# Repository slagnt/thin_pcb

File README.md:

# thin_pcb
5x5 pcb atmega32u4 smd

<a href="https://github.com/slagnt/thin_pcb/raw/master/pdf/thin_pcb.pdf">Eeschema PDF</a>

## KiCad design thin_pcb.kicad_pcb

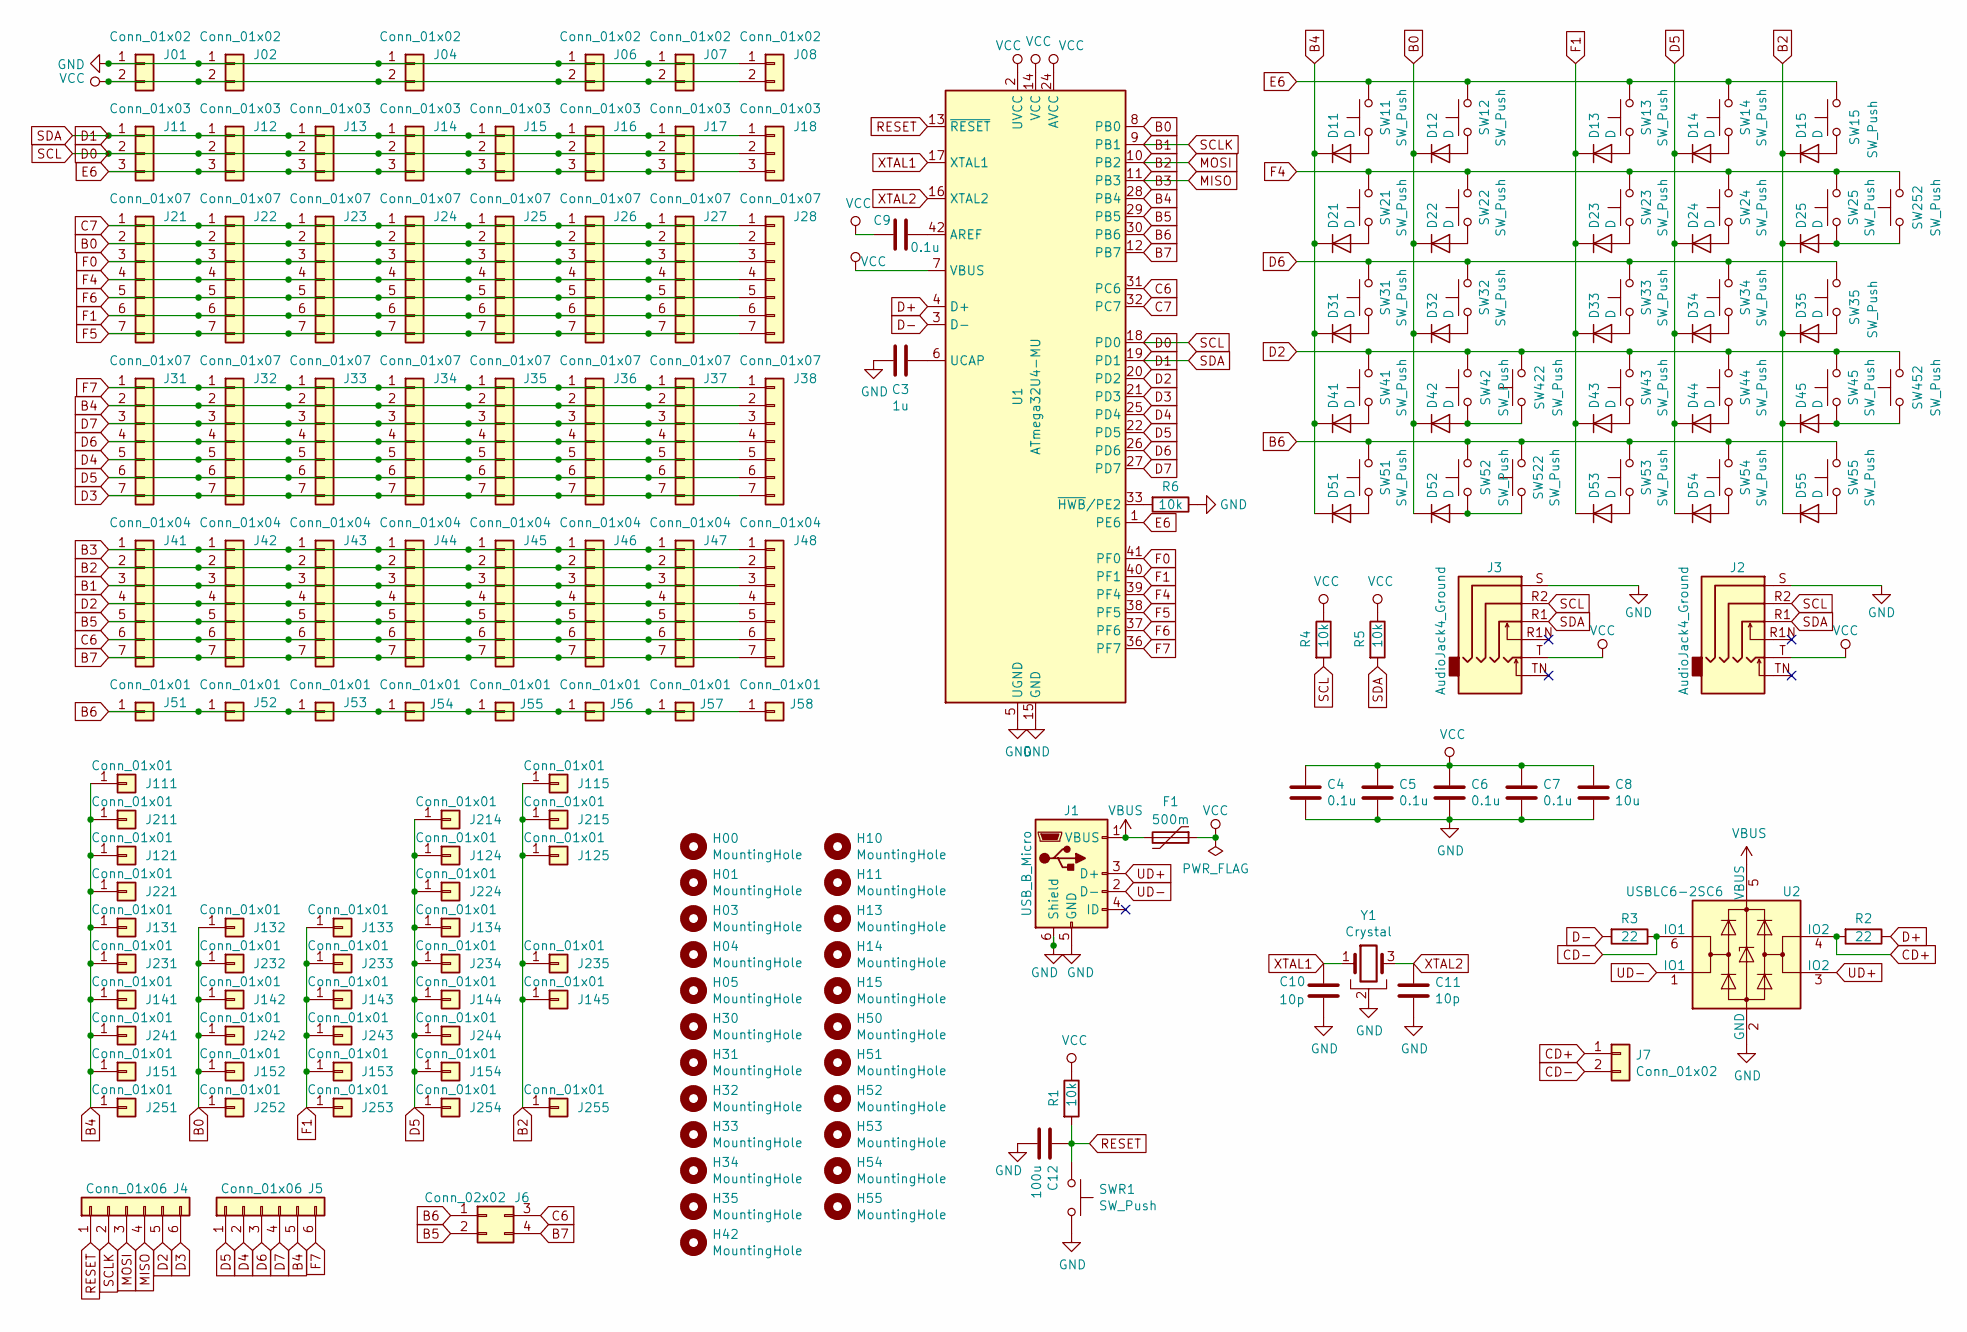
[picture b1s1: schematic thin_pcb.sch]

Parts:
C3: 1u; C_0402_1005Metric
C4, C5, C6, C7, C9: 0.1u; C_0402_1005Metric
C8: 10u; C_0402_1005Metric
C10, C11: 10p; C_0402_1005Metric
C12: 100u; C_0402_1005Metric
D11, D12, D13, D14, D15, D21, D22, D23, D24, D25, D31, D32, D33, D34, D35, D41, D42, D43, D44, D45, D51, D52, D53, D54, D55: D; D_MiniMELF
F1: 500m; Fuse_0603_1608Metric
H00, H01, H03, H04, H05, H10, H11, H13, H14, H15, H30, H31, H32, H33, H34, H35, H42, H50, H51, H52, H53, H54, H55: MountingHole; MountingHole_4mm
J1: USB_B_Micro; USB_Micro-B_Amphenol_10103594-0001LF_Horizontal
J01, J02, J04, J06, J7, J07, J08: Conn_01x02; PinSocket_1x02_P2.54mm_Vertical
J2, J3: AudioJack4_Ground; Jack_2.5mm_PJ242
J4, J5: Conn_01x06; PinSocket_1x06_P2.54mm_Vertical
J6: Conn_02x02; PinSocket_2x02_P2.54mm_Vertical
J11, J12, J13, J14, J15, J16, J17, J18: Conn_01x03; PinSocket_1x03_P2.54mm_Vertical
J21, J22, J23, J24, J25, J26, J27, J28, J31, J32, J33, J34, J35, J36, J37, J38: Conn_01x07; PinSocket_1x07_P2.54mm_Vertical
J41, J42, J43, J44, J45, J46, J47, J48: Conn_01x04; PinSocket_1x07_P2.54mm_Vertical
J51, J52, J53, J54, J55, J56, J57, J58, J111, J115, J121, J124, J125, J131, J132, J133, J134, J141, J142, J143, J144, J145, J151, J152, J153, J154, J211, J214, J215, J221, J224, J231, J232, J233, J234, J235, J241, J242, J243, J244, J251, J252, J253, J254, J255: Conn_01x01; PinSocket_1x01_P2.54mm_Vertical
R1, R4, R5, R6: 10k; R_0402_1005Metric
R2, R3: 22; R_0402_1005Metric
SW11, SW12, SW13, SW14, SW15, SW21, SW22, SW23, SW24, SW25, SW31, SW32, SW33, SW34, SW35, SW41, SW42, SW43, SW44, SW45, SW51, SW52, SW53, SW54, SW55, SW252, SW452: SW_Push; MX-Alps-Choc-1U-Mine
SW422, SW522: SW_Push; MX-Alps-Choc-1U-Mine-Flip
SWR1: SW_Push; SW_Reset
U1: ATmega32U4-MU; QFN-44-1EP_7x7mm_P0.5mm_EP5.2x5.2mm
U2: USBLC6-2SC6; SOT-23-6
Y1: Crystal; Resonator_SMD_muRata_CSTxExxV-3Pin_3.0x1.1mm

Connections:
B0: D12.1 (K), D22.1 (K), D32.1 (K), D42.1 (K), D52.1 (K), J21.2, J22.2, J23.2, J24.2, J25.2, J26.2, J27.2, J28.2, J132.1, J142.1, J152.1, J232.1, J242.1, J252.1, U1.8 (PB0)
B1: J4.2, J41.3, J42.3, J43.3, J44.3, J45.3, J46.3, J47.3, J48.3, U1.9 (PB1)
B2: D15.1 (K), D25.1 (K), D35.1 (K), D45.1 (K), D55.1 (K), J4.3, J41.2, J42.2, J43.2, J44.2, J45.2, J46.2, J47.2, J48.2, J115.1, J125.1, J145.1, J215.1, J235.1, J255.1, U1.10 (PB2)
B3: J4.4, J41.1, J42.1, J43.1, J44.1, J45.1, J46.1, J47.1, J48.1, U1.11 (PB3)
B4: D11.1 (K), D21.1 (K), D31.1 (K), D41.1 (K), D51.1 (K), J5.5, J31.2, J32.2, J33.2, J34.2, J35.2, J36.2, J37.2, J38.2, J111.1, J121.1, J131.1, J141.1, J151.1, J211.1, J221.1, J231.1, J241.1, J251.1, U1.28 (PB4)
B5: J6.2, J41.5, J42.5, J43.5, J44.5, J45.5, J46.5, J47.5, J48.5, U1.29 (PB5)
B6: J6.1, J51.1, J52.1, J53.1, J54.1, J55.1, J56.1, J57.1, J58.1, SW51.2, SW52.2, SW53.2, SW54.2, SW55.2, SW522.2, U1.30 (PB6)
B7: J6.4, J41.7, J42.7, J43.7, J44.7, J45.7, J46.7, J47.7, J48.7, U1.12 (PB7)
C6: J6.3, J41.6, J42.6, J43.6, J44.6, J45.6, J46.6, J47.6, J48.6, U1.31 (PC6)
C7: J21.1, J22.1, J23.1, J24.1, J25.1, J26.1, J27.1, J28.1, U1.32 (PC7)
CD+: J7.1, R2.2, U2.4 (IO2)
CD-: J7.2, R3.1, U2.6 (IO1)
D0: J2.R2, J3.R2, J11.2, J12.2, J13.2, J14.2, J15.2, J16.2, J17.2, J18.2, R4.2, U1.18 (PD0)
D1: J2.R1, J3.R1, J11.1, J12.1, J13.1, J14.1, J15.1, J16.1, J17.1, J18.1, R5.2, U1.19 (PD1)
D2: J4.5, J41.4, J42.4, J43.4, J44.4, J45.4, J46.4, J47.4, J48.4, SW41.2, SW42.2, SW43.2, SW44.2, SW45.2, SW422.2, SW452.2, U1.20 (PD2)
D3: J4.6, J31.7, J32.7, J33.7, J34.7, J35.7, J36.7, J37.7, J38.7, U1.21 (PD3)
D4: J5.2, J31.5, J32.5, J33.5, J34.5, J35.5, J36.5, J37.5, J38.5, U1.25 (PD4)
D5: D14.1 (K), D24.1 (K), D34.1 (K), D44.1 (K), D54.1 (K), J5.1, J31.6, J32.6, J33.6, J34.6, J35.6, J36.6, J37.6, J38.6, J124.1, J134.1, J144.1, J154.1, J214.1, J224.1, J234.1, J244.1, J254.1, U1.22 (PD5)
D6: J5.3, J31.4, J32.4, J33.4, J34.4, J35.4, J36.4, J37.4, J38.4, SW31.2, SW32.2, SW33.2, SW34.2, SW35.2, U1.26 (PD6)
D7: J5.4, J31.3, J32.3, J33.3, J34.3, J35.3, J36.3, J37.3, J38.3, U1.27 (PD7)
D+: R2.1, U1.4 (D+)
D-: R3.2, U1.3 (D-)
E6: J11.3, J12.3, J13.3, J14.3, J15.3, J16.3, J17.3, J18.3, SW11.2, SW12.2, SW13.2, SW14.2, SW15.2, U1.1 (PE6)
F0: J21.3, J22.3, J23.3, J24.3, J25.3, J26.3, J27.3, J28.3, U1.41 (PF0)
F1: D13.1 (K), D23.1 (K), D33.1 (K), D43.1 (K), D53.1 (K), J21.6, J22.6, J23.6, J24.6, J25.6, J26.6, J27.6, J28.6, J133.1, J143.1, J153.1, J233.1, J243.1, J253.1, U1.40 (PF1)
F4: J21.4, J22.4, J23.4, J24.4, J25.4, J26.4, J27.4, J28.4, SW21.2, SW22.2, SW23.2, SW24.2, SW25.2, SW252.2, U1.39 (PF4)
F5: J21.7, J22.7, J23.7, J24.7, J25.7, J26.7, J27.7, J28.7, U1.38 (PF5)
F6: J21.5, J22.5, J23.5, J24.5, J25.5, J26.5, J27.5, J28.5, U1.37 (PF6)
F7: J5.6, J31.1, J32.1, J33.1, J34.1, J35.1, J36.1, J37.1, J38.1, U1.36 (PF7)
GND: C3.2, C4.1, C5.1, C6.1, C7.1, C8.1, C10.1, C11.1, C12.1, J01.1, J1.5 (GND), J1.6 (Shield), J02.1, J2.S, J3.S, J04.1, J06.1, J07.1, J08.1, R6.1, SWR1.2, U1.5 (UGND), U1.15 (GND), U1.23 (GND), U1.35 (GND), U1.43 (GND), U1.45 (GND), U2.2 (GND), Y1.2
unnamed: C3.1, U1.6 (UCAP)
unnamed: C9.2, U1.42 (AREF)
unnamed: D11.2 (A), SW11.1
unnamed: D12.2 (A), SW12.1
unnamed: D13.2 (A), SW13.1
unnamed: D14.2 (A), SW14.1
unnamed: D15.2 (A), SW15.1
unnamed: D21.2 (A), SW21.1
unnamed: D22.2 (A), SW22.1
unnamed: D23.2 (A), SW23.1
unnamed: D24.2 (A), SW24.1
unnamed: D25.2 (A), SW25.1, SW252.1
unnamed: D31.2 (A), SW31.1
unnamed: D32.2 (A), SW32.1
unnamed: D33.2 (A), SW33.1
unnamed: D34.2 (A), SW34.1
unnamed: D35.2 (A), SW35.1
unnamed: D41.2 (A), SW41.1
unnamed: D42.2 (A), SW42.1, SW422.1
unnamed: D43.2 (A), SW43.1
unnamed: D44.2 (A), SW44.1
unnamed: D45.2 (A), SW45.1, SW452.1
unnamed: D51.2 (A), SW51.1
unnamed: D52.2 (A), SW52.1, SW522.1
unnamed: D53.2 (A), SW53.1
unnamed: D54.2 (A), SW54.1
unnamed: D55.2 (A), SW55.1
unnamed: R6.2, U1.33 (~HWB~/PE2)
RESET: C12.2, J4.1, R1.2, SWR1.1, U1.13 (~RESET)
UD+: J1.3 (D+), U2.3 (IO2)
UD-: J1.2 (D-), U2.1 (IO1)
VBUS: F1.2, J1.1 (VBUS), U2.5 (VBUS)
VCC: C4.2, C5.2, C6.2, C7.2, C8.2, C9.1, F1.1, J01.2, J02.2, J2.T, J3.T, J04.2, J06.2, J07.2, J08.2, R1.1, R4.1, R5.1, U1.2 (UVCC), U1.7 (VBUS), U1.14 (VCC), U1.24 (AVCC), U1.34 (VCC), U1.44 (AVCC)
XTAL1: C10.2, U1.17 (XTAL1), Y1.1
XTAL2: C11.2, U1.16 (XTAL2), Y1.3

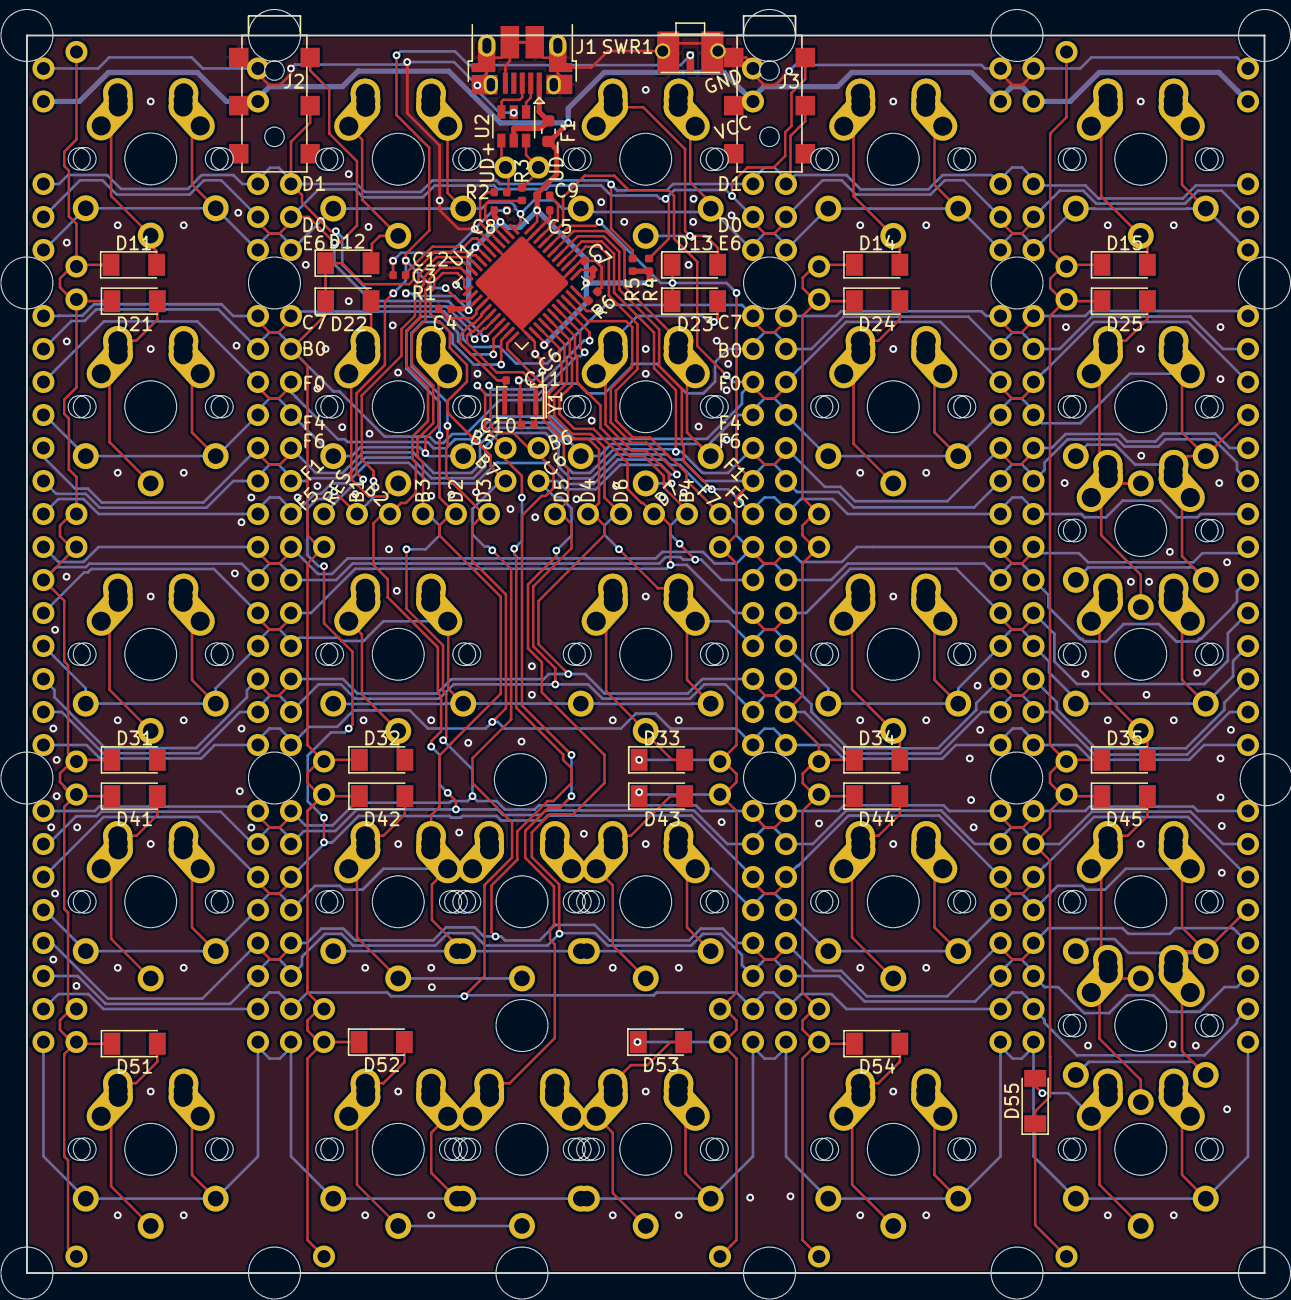
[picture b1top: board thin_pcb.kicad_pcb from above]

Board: 2 copper layers, 95.2 x 95.2 mm, 188 parts (0 on the bottom side), 65 nets.

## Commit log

2019-06-29 init
2019-07-01 spi traces
2019-07-02 connectors pins
2019-07-03 draft
2019-07-03 schema
2019-07-03 arrange schema
2019-07-04 labels, mountingholes
2019-07-05 fix circuits labels
2019-07-09 reset pinhole
2019-07-10 breakline
2019-07-11 breaklines
2019-07-15 hide unwanted labels
2019-07-16 pin labels
2019-07-16 3d pics
2019-07-20 smd 0603->1005 & fixes
2019-07-20 add imgs to readme
2019-07-20 aref cond & positioning
2019-07-20 some traces aligning
2019-07-20 fixes
2019-07-20 reset switch & aligning
2019-07-20 aligning
2019-07-30 pcb class 0.2
2019-07-30 column pins
2019-07-31 remove 90 angles
2019-08-01 breakline & vcc
2019-08-02 bug fixes
2019-09-01 gnd area
2019-09-21 costar
